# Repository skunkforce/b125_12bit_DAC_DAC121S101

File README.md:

# edgy_board number b125
This design is part of the [edgy board project](https://github.com/skunkforce/edgy_boards).

# getting started
This repository uses submodules. After cloning use the command 

```$ git submodule update --init --recursive```

to pull the submodules before opening the project with kicad. 

# Tests
Tests can be found in [TESTS.md](TESTS.md)

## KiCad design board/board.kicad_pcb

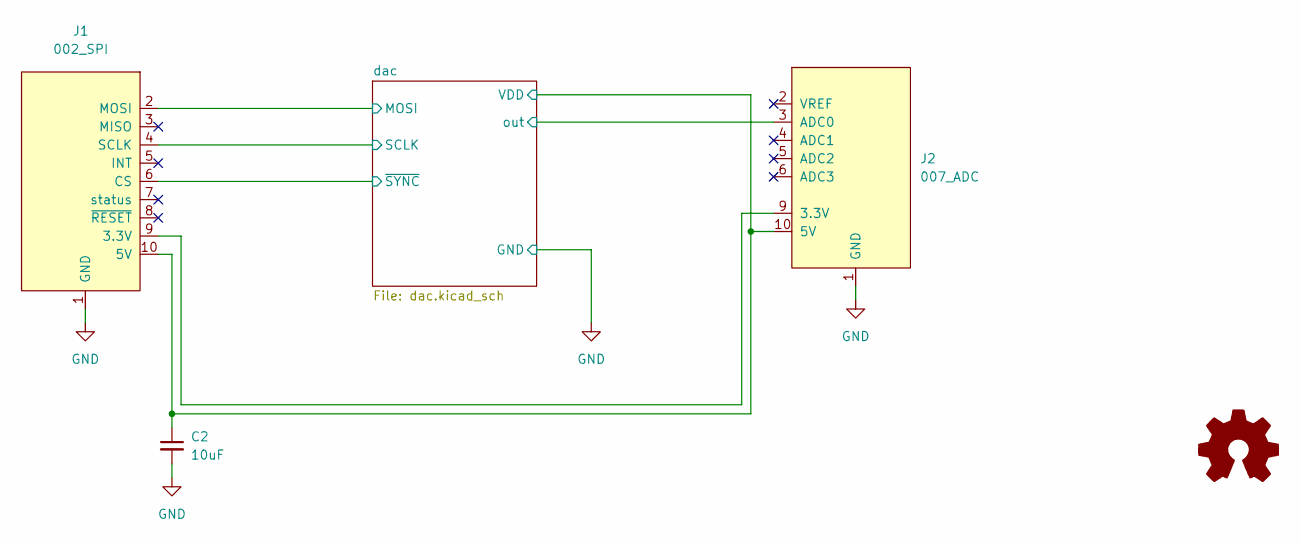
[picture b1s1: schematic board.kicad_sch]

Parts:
C2: 10uF; C_0603_1608Metric
J1: 002_SPI; on_edge_2x05_device
J2: 007_ADC; on_edge_2x05_host
LOGO1: Logo_Open_Hardware_Small; OSHW-Symbol_6.7x6mm_SilkScreen

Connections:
/dac/MOSI: J1.2 (MOSI); also elsewhere on the board
/dac/SCLK: J1.4 (SCLK); also elsewhere on the board
/dac/VDD: C2.1, J1.10 (5V), J2.10 (5V); also elsewhere on the board
/dac/out: J2.3 (ADC0); also elsewhere on the board
/dac/~SYNC: J1.6 (CS); also elsewhere on the board
GND: C2.2, J1.1 (GND), J2.1 (GND); also elsewhere on the board
unnamed: J1.9 (3.3V), J2.9 (3.3V)

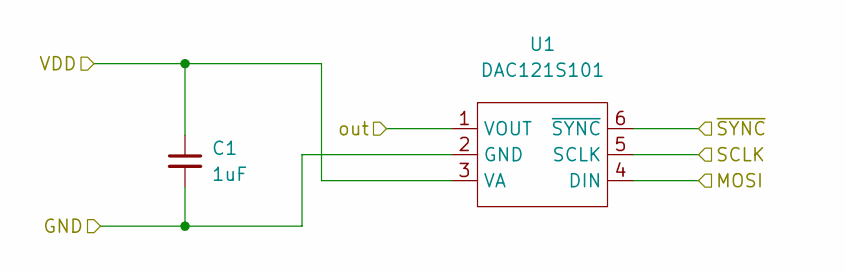
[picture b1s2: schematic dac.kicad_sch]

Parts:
C1: 1uF; C_0603_1608Metric
U1: DAC121S101; SOT-23-6; MPN DAC121S101CIMKX/NOPB; Digi-Key_PN 296-38083-1-ND

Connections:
/dac/MOSI: U1.4 (DIN); also elsewhere on the board
/dac/SCLK: U1.5 (SCLK); also elsewhere on the board
/dac/VDD: C1.1, U1.3 (VA); also elsewhere on the board
/dac/out: U1.1 (VOUT); also elsewhere on the board
/dac/~SYNC: U1.6 (~SYNC); also elsewhere on the board
GND: C1.2, U1.2 (GND); also elsewhere on the board

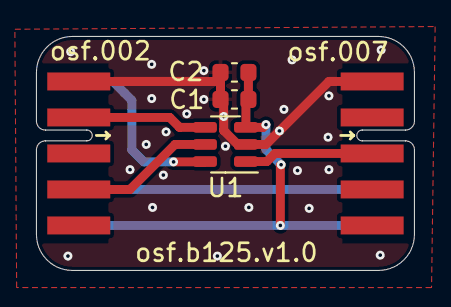
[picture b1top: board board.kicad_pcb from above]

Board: 2 copper layers, 21.0 x 13.0 mm, 6 parts (1 on the bottom side), 7 nets.

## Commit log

2023-04-13 initial
